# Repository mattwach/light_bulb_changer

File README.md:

# Light Bulb Changer

_Note: I also made a [video describing the project](https://youtu.be/A-EdzPTZSjM)._

Do you have hard-to-reach light bulbs?  If so, then you are perhaps familiar a
_Light Bulb Changer_.  It threads on the end of a pole and extends your reach. 
A problem is one of mechanics.  If you can't get your pole square to the bulb,
the effectiveness of the holder decreases rapidly.  Imagine trying to use
this thing at a 90 degree angle to the bulb.  That is the exact situation I
found myself in: 

OK. Just get a tall ladder, move that table, make that suspicious call
confirming my life insurance details and up I go.  Just kidding, I instead
used this as an excuse for another maker project.

I spent way more time on this than the ladder would have taken.  Then again, it
was quite a bit of fun and now I have a useful tool on-hand ready to square off
against the next light bulb challenge.  Lucky for you, all of the design,
modeling, and testing steps are done so you can build one in a fraction of the time.
Heck, I even include a walkthrough below.

Of course if you want extra challenge, feel free to mod up the design below to
match your favorite parts and techniques.  Have it play inspirational music, add
Bluetooth for some reason... Your imagination, skill, time and budget are your
only limits.

If you don't have a 3D printer, hope is not lost.  You can always use a project
box, parts from the hardware store and plenty of zip ties to get things done old
school.

## Step 1: Parts

Here is what I built:

The middle unit is a motorized driver that the light bulb changer screws onto.
It then screws on a pole.  Now you have both a motor and a way to change the
angle.  There is also a control box that goes on the other end of the pole.

### Parts I used include:

   1. **[Geared brushed motor](https://www.amazon.com/gp/product/B0728HDH45)**.  These
      are around $13 on Amazon, probably cheaper other places.  I went with 200
      RPM which is a bit more than 3 rotations/second at 12V.  This seemed about
      right.
   2. **[Flange Coupling Connector](https://smile.amazon.com/gp/product/B07PDYV4P3)**. 
      This is needed to adapt the motor's shaft to the _Light Bulb Changer_.
   3. **Microcontroller**. I went with the [ATTiny85](https://www.sparkfun.com/products/9378)
      Loading firmware on it can be tricky if you have not done so before.  But there are
      dozens of video and written guides on the internet on how to do it.  Once you
      get it working the first time, it will be turn key after that.
   4. **[L293D](https://www.adafruit.com/product/807) H-bridge motor driver**.
      This turns the puny waveforms the ATTiny85 can generate into power boosted
      energy waves that can drive a motor at variable speeds and in either forward
      or reverse.
   5. **Broomstick** for mounting
   6. **[Enough wire](https://www.amazon.com/BNTECHGO-Flexible-Conductor-Resistant-Extension/dp/B077X9MVWG)**
      to reach all the way down the broomstick.
   7. **Zipties** to secure the control module to the broomstick.
   8. **[Sony PS2 thumbstick](https://www.amazon.com/HiLetgo-Controller-JoyStick-Breakout-Arduino/dp/B00P7QBGD2)**
      which is basically a thumb-friendly potentiometer. Any 10k potentiometer will work,
      so long as you can handle the ergonomics.
   9. **A power source**.  You'll need around 12V and enough current to keep the motor
      happy.  A [3S lipo battery](https://www.amazon.com/TATTU-Battery-650mAh-Torrent-Lizard/dp/B071GBGBB4)
      (450-1800 mAh) fits this bill perfectly, but you'll need a special charger if you don't already
      have one.  You can also stack 9 (or more) AA batteries in series.  A 12V DC wall wart could also work.
   10. **Connectors for the power source**.  With a small 3S LIPO, I really like
       the [XT30 connector](https://www.amazon.com/10Pairs-Upgrade-Connector-Female-Battery/dp/B08P5HVMYT)
       and that is what the 3D printed case is designed to handle without
       "manual modifications"
   11. **PCB prototyping board** - Technically optional as there are so many way to construct a circuit.
       But a [30x70 perf board](https://www.amazon.com/ELEGOO-Prototype-Soldering-Compatible-Arduino/dp/B072Z7Y19F)
       is my personal preference.
   12. **Status LED(s)**.  I went with a two-color LED which has red and green
       channels.  You can also go with two separate LEDs of any color you want with minimal changes.
   13. **Some current limiting resistors** for the LEDs.  Values are not critical -
       something in the 470 to 2k range will work.
   14. **A 5V regulator**.  I went with the LP2950Z but [nearly anything](https://www.sparkfun.com/products/107)
       will work here. 
   15. **Some capacitors**.  The DC motor is a noisy load for the battery and the 5V
       regulator will see this noise on it's input.  Caps on each side of the
       regulator will help reduce this noise to the 5V electronics  I went with
       500+ uF on the input side and another 100 uF on the output side, which is
       likely overkill.
   16. **Connectors** for the PS2 thumbstick and motor wire.  I used standard 2.54mm pitch
       headers.  Anything you have could work.

### Tools you'll need:

   1. **A 3D printer** if you want print the motor housing and controller box.  As
      said above, you can also come up with a custom alternate solution.
   2. **A Breadboard** if you want to verify operation before committing the parts with
      solder.

## Step 2: Electronics Overview

The ordering is not strict here but I like getting the electronics working
first.  A breadboard is a good way to wire things up and some confidence
that the project is on the right track.

Here is the schematic:

You do not need to starting wiring up the breadboard yet, as upcoming steps
will break that down into smaller steps

So how does this thing work?

   * You move the potentiometer (PS2 thumbstick, top of schematic)
   * The ATTiny85 microcontroller notes the new potentiometer state (via `PB4`)
     and uses it to update the motor direction and speed. 
   * The direction and speed are communicated via a PWM signal (via `PB0`) which
     tells the motor how fast to spin via the only language it understands: power.
     The microcontroller also sends a signal (via PB1 and PB2) that tells the motor
     controller which polarity to send to the motor.
   * The L293D motor controller (right) takes the weak PWM signal from the microcontroller and
     puts the full force of the battery pack behind it (e.g. 12V and whatever
     current the motor asks for - within obvious limits..)
   * The bottom left of the circuit is just the 5V regulator and some supporting
     capacitors to filter out motor noise.

You can probably imagine the rest - adapter on motor, light bulb changer on
adapter and light.  Turning, problems being solved, happy time.

## Step 3: ATTiny85 Programming and Testing

The code is located in the `firmware/` directory.  This code is not Arduino so
you will need to have/develop familiarity with `avr-gcc` to compile it.  But,
**you don't have to compile it** because there is an already-compiled
`firmware/prebuilt/light_bulb_changer.hex` file ready to go.

Loading code onto the ATTiny85 involves conforming to the protocol specified in
its
[datasheet](https://ww1.microchip.com/downloads/en/DeviceDoc/Atmel-2586-AVR-8-bit-Microcontroller-ATtiny25-ATtiny45-ATtiny85_Datasheet.pdf).
There are several possible solutions and a large amount of websites and Youtube
videos that cover the topic.

A sampling of options include:

   1. The official AVR programming tools
   2. [Using an Arduino Uno (or nano) *as a programmer*](https://create.arduino.cc/projecthub/arjun/programming-attiny85-with-arduino-uno-afb829)
   3. [Using the Sparkfun ATTiny85 programmer](https://learn.sparkfun.com/tutorials/tiny-avr-programmer-hookup-guide/all)

I personally went with a variation of option #2, using an Arduino Nano and
a [test clip](https://www.amazon.com/Pomona-Electronics-5250-Plated-Spacing/dp/B00JJ4G13I):

The three guides I listed above assume that you want to use the Arduino framework to
_write code_ for the ATTiny85.  Maybe you do, but Arduino can not compile the code here
and you already have a compiled `light_bulb_changer.hex` file ready to upload so compiling
it again is not needed.

Still it's convenient to follow the steps because as a part of the exercise,
you'll end up with a copy of the
[avrdude](https://www.nongnu.org/avrdude/) code uploading tool as well as
examples of how to use it.

When you run the "blinking light" example of one of the guides above, the
Arduino console will output the `avrdude` command it used.  This can be compared
to the one I used (which is also in `firmware/prebuilt/README`):

    # in the firmware/prebuilt directory:

    /usr/bin/avrdude \
      -C./avrdude.conf \
      -v \
      -pattiny85 \
      -cstk500v1 \
      -P /dev/ttyUSB0 \
      -b19200 \
      -Uflash:w:light_bulb_changer.hex:i

Depending on the programming tools you have and the OS you
are using, some flags will be different and you'll want to combine the
flags from the blinking light example with the `-Uflash:w:light_bulb_changer.hex:i`
option above.

OK, now that we are through all of that, I suggest a simple verification on the
breadboard.  We will wire up a simplified version of the schematic as shown:

This follows the original schematic but with the motor enable (pin 1 of the
    L293D) replaced with a white LED and the potentiometer replaced with a
resistor to ground.  Specifically:

   * Pin 1 (Reset) Not Connected
   * Pin 2 (Pot input) -> Resistor -> Ground
   * Pin 3 Not Connected
   * Pin 4 (`GND`) -> Ground
   * Pin 5 (`PWM`) -> Resistor -> White LED -> Ground
   * Pin 6 (Forward) -> Resistor -> Greed LED -> Ground
   * Pin 7 (Reverse) -> Resistor -> Red LED -> Ground
   * Pin 8 (5V) -> Some voltage between 2V-5.5V

What resistor values?  Anything in the 400-5K range is fine for the LEDs.
Anything at all is fine for Pin 2.

What we should see is the green and white LEDs lit up.  The firmware thinks that
the motor is in full-power forward mode because we have Pin 2 grounded.

Now lets, make one change.  Instead of grounding Pin 2, connect it to power:

Now the ATTiny85 thinks it need to drive the motor full power in reverse.

You could call the testing "done" at this point, but I'm going to take it a
little further for educational purposes.  Here I connected a real potentiometer
to pin 2 (I didn't go with the PS2 thumbstick just yet because I wanted to
    potentiometer to stay at a certain value for the test).  I also added
an oscilloscope probe to pin 5:

Now the potentiometer can be used to change between forward and reverse, just
like the final product.  It's also possible to see the white LED getting
darker and brighter but this is more obvious from the oscilloscope.  Here
is a scope image at "low power", where the motor will turn more slowly.  Note
how the signal spends most of it's time at 0V:

Here, the potentiometer is turned further to the left (or right since there
is both a forward and reverse).  More time at 5V means more motor speed:

and finally, the highest power setting shows the signal at 5V the whole time:

## Step 4: Building the PCB

Repeating the schematic:

Here is a board layout that represent my own strategy for building the PCB:

Actual built-up part:

Of course, you can build the board any way you want.  Just keep in mind that
the 3D printed control box is sized to house a PCB that is 30mm x 51mm.  This
size could (technically) be changed in the `3d_print/motor_controller_pcb.scad`
file by someone who is willing to do some OpenSCAD work.
 
## Step 5: 3D Print Control Box and Motor Carriage

There are two directories of interest.  

The one named `stl/` contains already-rendered parts.

The other one is named `openscad/`.  If
you just want the parts, _you can ignore this directory_.  If you want to
customize the parts, you'll need the (free) OpenSCAD software.  The main
files of interest are `openscad/control_box_assembly.scad` and
`openscad/motor_assembly.scad`.  Scroll to the bottom of each file
and note the comments.

Here is a inventory of each part:

Starting with the motor box, we have a threaded interface to the light
bulb removal tool (`threaded_attachment.stl`):

Next, the carriage for the motor (`motor_carriage.stl`):

And a cover for the motor carriage (`motor_carriage_cover.stl`):

And finally an interface between the motor carriage and pole (`pole_interface.stl`) 

Onto the control box.  This consists of three components held together by 16mm
M3 bolts.  First the pole interface, which is intended to be held on with
zip ties (`control_box_interface.stl`):

Next, the middle section, which holds all of the electronics (`control_box_bottom.stl`):

And finally the top cover (`control_box_top.stl`):

Here is everything assembled:

## Step 6: Final Assembly

Here is an rendered and actual image of the control box assembly.  Refer to the
previous steps for more details on the electrical connections.

Here are some images to show how the motor assembly is supposed to work:

Note that if the motor is spinning the wrong way, you can just reverse the
motor connection at the control box (NOT the battery connection).

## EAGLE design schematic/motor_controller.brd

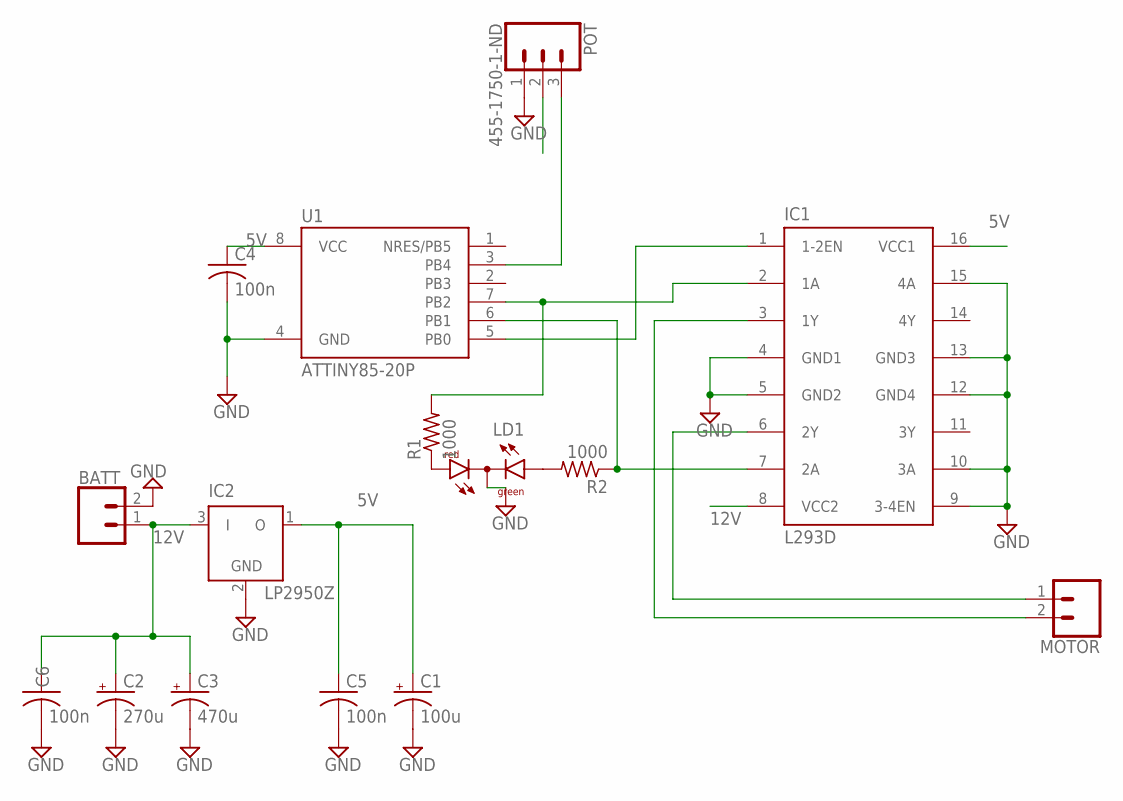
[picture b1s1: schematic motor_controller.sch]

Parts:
BATT: CONN_02; 1X02
C1: 100u; E3,5-10
C2: 270u; E3,5-10
C3: 470u; E3,5-10
C4, C5, C6: 100n; C050-055X075
IC1: L293D; DIL16
IC2: LP2950Z; TO92
LD1: DUOLED-RG-C; DUOLED-C-5MM
MOTOR: CONN_02; 1X02
POT: 455-1750-1-ND; 1X03
R1, R2: 1000; 0204/7
U1: ATTINY85-20P; PDIP08_300MIL

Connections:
5V: C1.+, C4.1, C5.1, IC1.16 (VCC1), IC2.1 (O), POT.2, U1.8 (VCC)
12V: BATT.1, C2.+, C3.+, C6.1, IC1.8 (VCC2), IC2.3 (I)
GND: BATT.2, C1.-, C2.-, C3.-, C4.2, C5.2, C6.2, IC1.4 (GND1), IC1.5 (GND2), IC1.9 (3-4EN), IC1.10 (3A), IC1.12 (GND4), IC1.13 (GND3), IC1.15 (4A), IC2.2 (GND), LD1.C, POT.1, U1.4 (GND)
unnamed: IC1.1 (1-2EN), U1.5 (PB0)
unnamed: IC1.6 (2Y), MOTOR.1
unnamed: IC1.3 (1Y), MOTOR.2
unnamed: IC1.7 (2A), R2.1, U1.6 (PB1)
unnamed: IC1.2 (1A), R1.2, U1.7 (PB2)
unnamed: LD1.AR, R1.1
unnamed: LD1.AX (AG), R2.2
unnamed: POT.3, U1.3 (PB4)

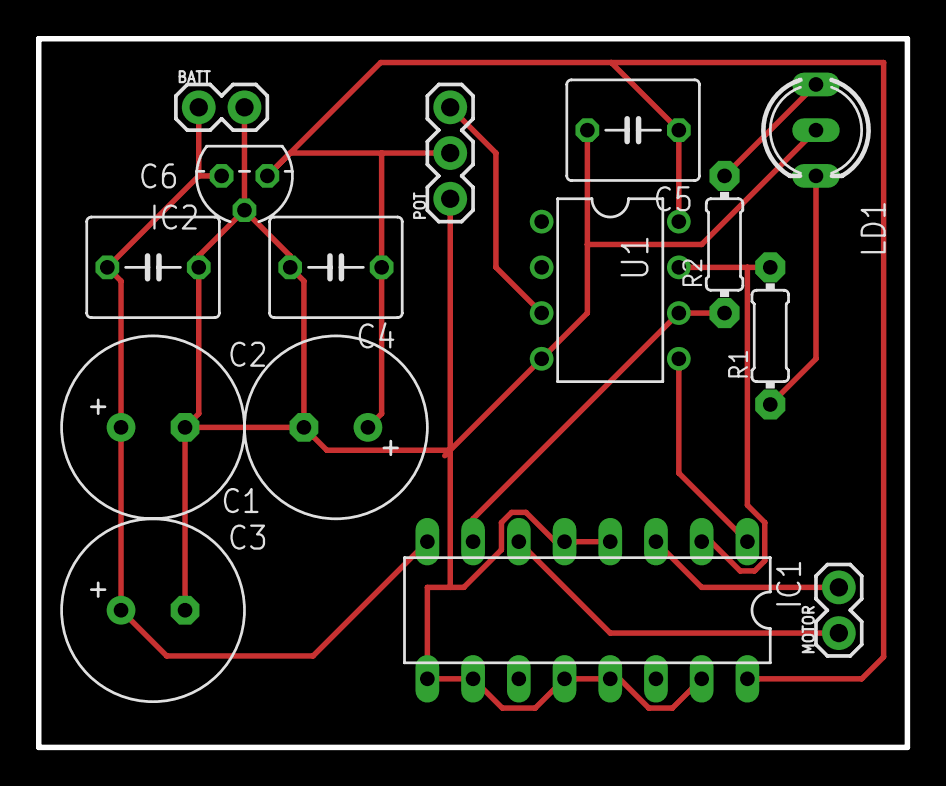
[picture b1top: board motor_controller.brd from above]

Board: 2 copper layers, 48.3 x 39.4 mm, 15 parts (0 on the bottom side), 11 nets.

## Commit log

2021-10-29 Added firmware, 3d print files and schematics.
2021-11-03 Added more content to the README instructions.
2021-11-06 Added prebuilt binaries
2021-11-07 Added instructions regarding ATTiny85 programming and test.
2021-11-09 Added wiring step
2021-11-13 Added 3D print instructions and STL models.
2021-11-17 Fiinshed draft of readme
2021-11-17 Spellcheck
2021-11-17 Moved video link
2021-11-17 Edit/cleanup pass of README
2021-12-08 Changed cover photo

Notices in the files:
parts and their libraries:
SparkFun-Connectors: Licensing: Creative Commons ShareAlike 4.0 International - https://creativecommons.org/licenses/by-sa/4.0
